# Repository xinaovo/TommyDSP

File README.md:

# TommyDSP

An audio DSP platform based on RP2350 microcontroller

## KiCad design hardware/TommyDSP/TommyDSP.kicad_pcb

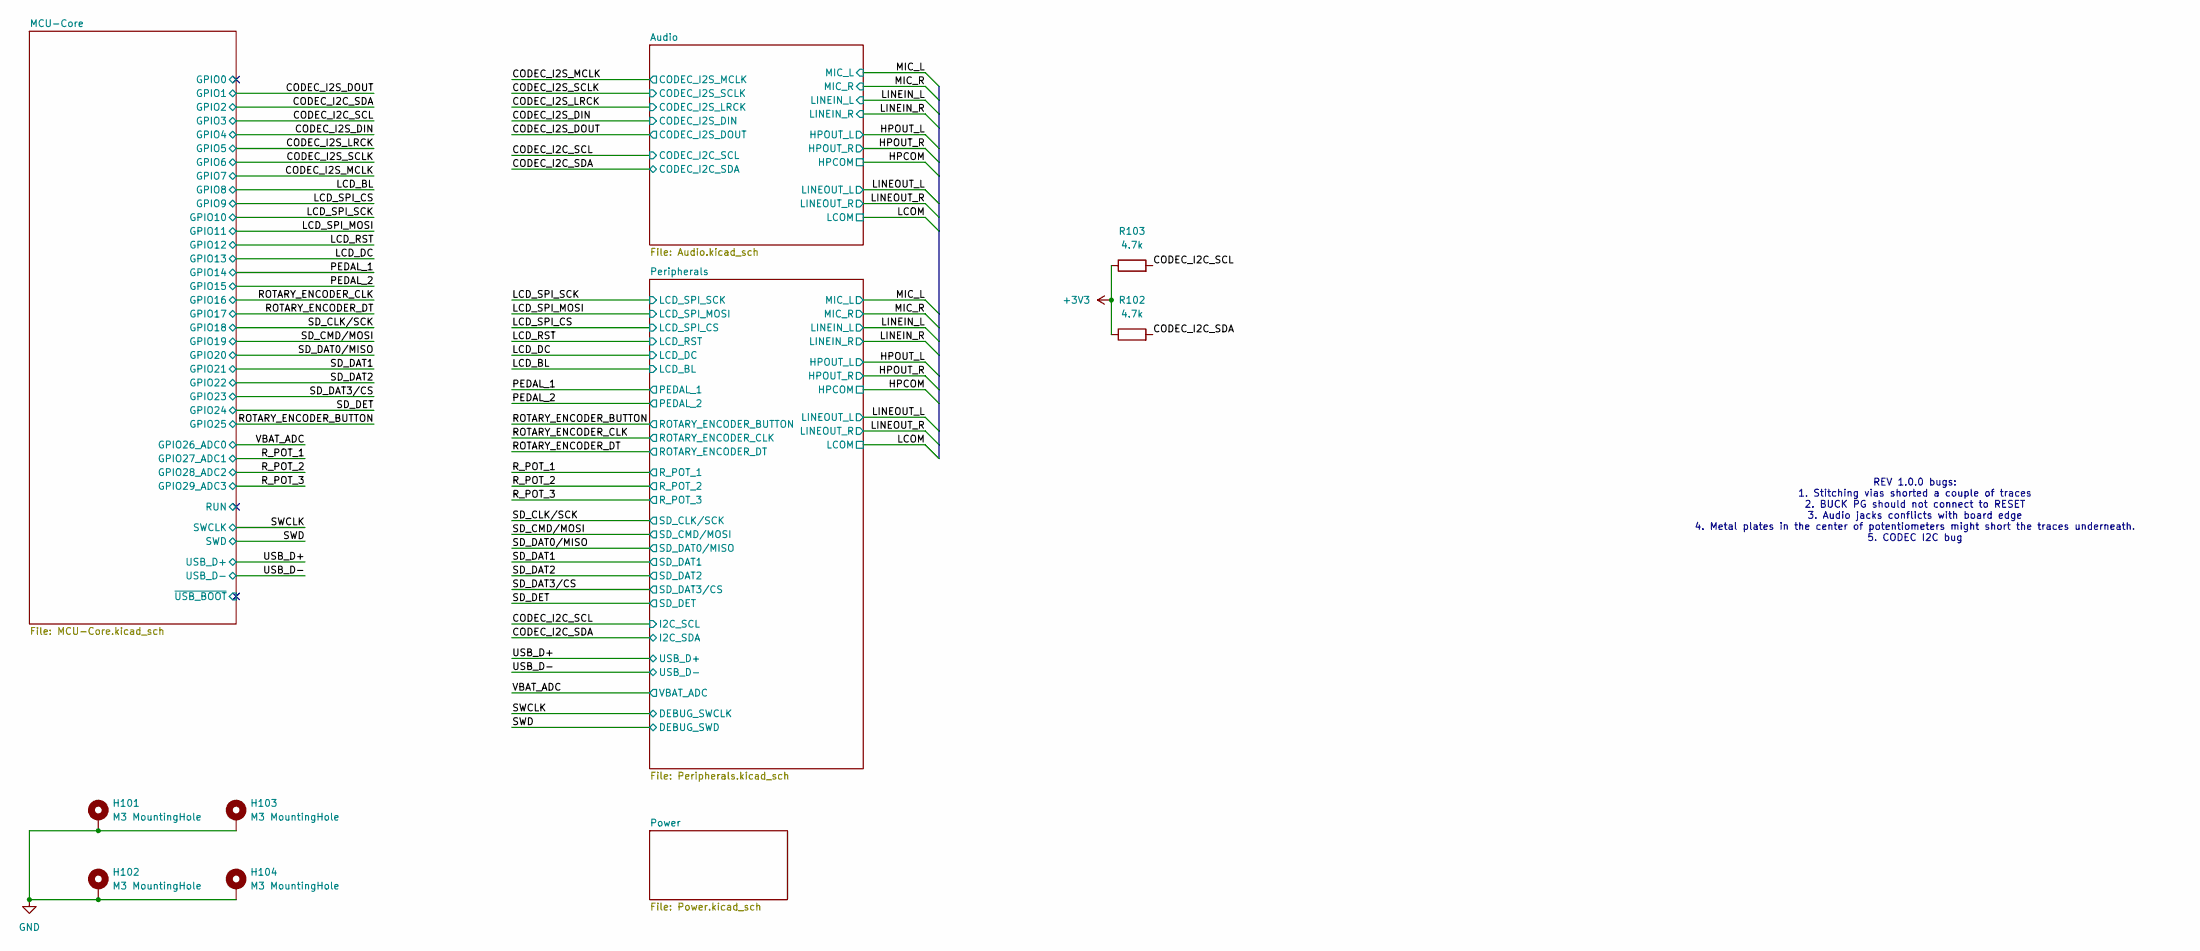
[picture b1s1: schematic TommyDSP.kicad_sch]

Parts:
H101, H102, H103, H104: M3 MountingHole; MountingHole_3.2mm_M3_DIN965_Pad_TopBottom
R102, R103: 4.7k; R_0603_1608Metric

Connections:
+3V3: R102.1, R103.1; also elsewhere on the board
/CODEC_I2C_SCL: R103.2; also elsewhere on the board
/CODEC_I2C_SDA: R102.2; also elsewhere on the board
GND: H101.1 (1_1), H102.1 (1_1), H103.1 (1_1), H104.1 (1_1); also elsewhere on the board

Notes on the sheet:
REV 1.0.0 bugs: 1. Stitching vias shorted a couple of traces 2. BUCK PG should not connect to RESET 3. Audio jacks conflicts with board edge 4. Metal plates in the center of potentiometers might short the traces underneath. 5. CODEC I2C bug

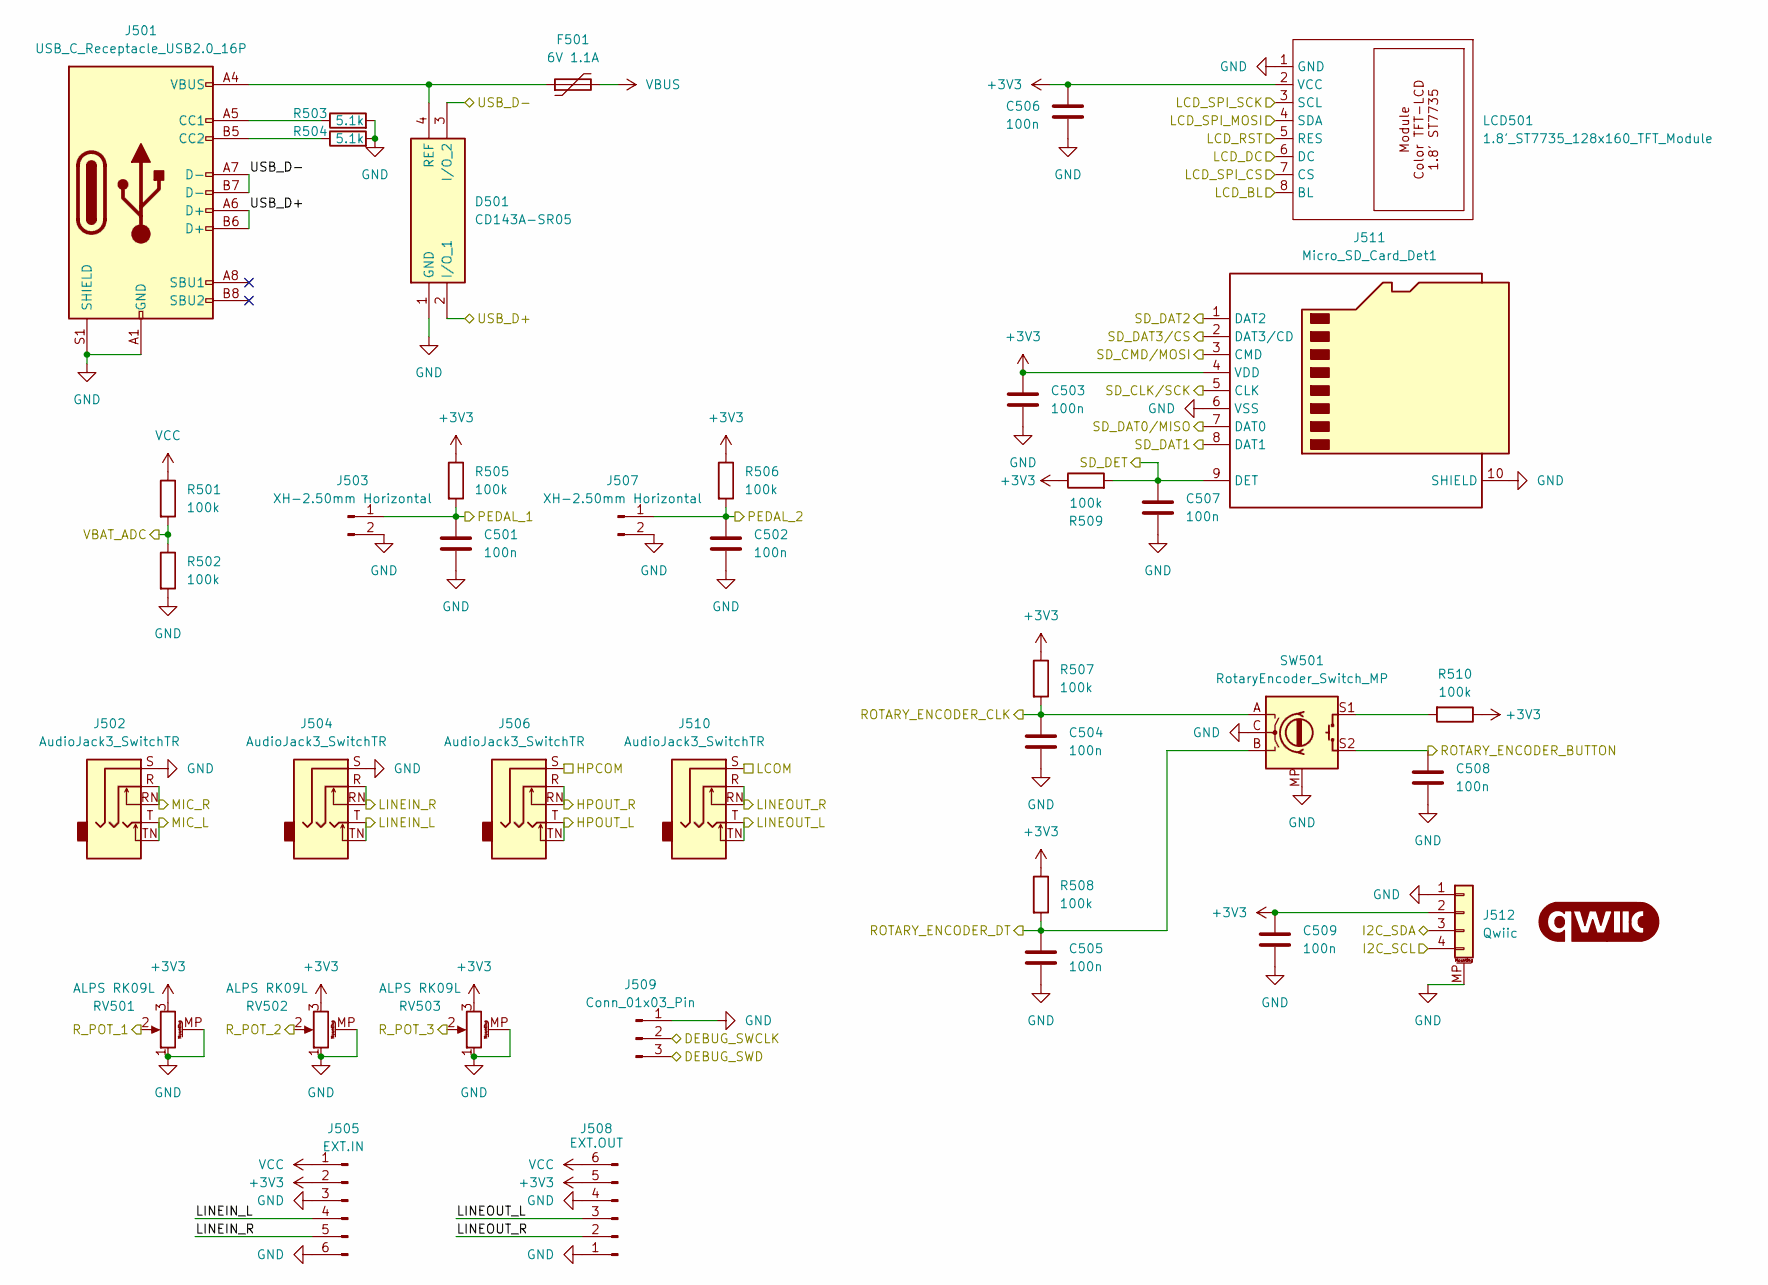
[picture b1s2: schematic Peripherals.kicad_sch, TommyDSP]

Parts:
C501, C502, C503, C504, C505, C506, C507, C508, C509: 100n; C_0603_1608Metric
D501: CD143A-SR05; CD143ASR05; Manufacturer_Part_Number CD143A-SR05; Mouser Part Number 652-CD143A-SR05
F501: 6V 1.1A; Fuse_1206_3216Metric
G501: qwiic_Logo; qwiic_5.5mm
J501: USB_C_Receptacle_USB2.0_16P; USB_C_Receptacle_G-Switch_GT-USB-7010ASV
J502, J504, J506, J510: AudioJack3_SwitchTR; Jack_3.5mm_CUI_SJ1-3525N_Horizontal
J503, J507: XH-2.50mm Horizontal; JST_EH_S2B-EH_1x02_P2.50mm_Horizontal
J505: EXT.IN; JST_XH_S6B-XH-A-1_1x06_P2.50mm_Horizontal
J508: EXT.OUT; JST_XH_S6B-XH-A-1_1x06_P2.50mm_Horizontal
J509: Conn_01x03_Pin; PinHeader_1x03_P2.54mm_Vertical
J511: Micro_SD_Card_Det1; TF01A
J512: Qwiic; JST_SH_SM04B-SRSS-TB_1x04-1MP_P1.00mm_Horizontal
LCD501: 1.8'_ST7735_128x160_TFT_Module
R501, R502, R505, R506, R507, R508, R509, R510: 100k; R_0603_1608Metric
R503, R504: 5.1k; R_0603_1608Metric
RV501, RV502, RV503: ALPS RK09L; Potentiometer_Alps_RK09K_Single_Vertical
SW501: RotaryEncoder_Switch_MP; RotaryEncoder_Alps_EC11E-Switch_Vertical_H20mm

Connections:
+3V3: C503.1, C506.1, C509.1, J505.2, J508.5, J511.4 (VDD), J512.2, LCD501.2 (VCC), R505.1, R506.1, R507.1, R508.1, R509.1, R510.1, RV501.3, RV502.3, RV503.3; also elsewhere on the board
/CODEC_I2C_SCL: J512.4; also elsewhere on the board
/CODEC_I2C_SDA: J512.3; also elsewhere on the board
/HPOUT_L: J506.T, J506.TN; also elsewhere on the board
/HPOUT_R: J506.R, J506.RN; also elsewhere on the board
/LCD_BL: LCD501.8 (BL); also elsewhere on the board
/LCD_DC: LCD501.6 (DC); also elsewhere on the board
/LCD_RST: LCD501.5 (RES); also elsewhere on the board
/LCD_SPI_CS: LCD501.7 (CS); also elsewhere on the board
/LCD_SPI_MOSI: LCD501.4 (SDA); also elsewhere on the board
/LCD_SPI_SCK: LCD501.3 (SCL); also elsewhere on the board
/LINEIN_L: J504.T, J504.TN, J505.4; also elsewhere on the board
/LINEIN_R: J504.R, J504.RN, J505.5; also elsewhere on the board
/LINEOUT_L: J508.3, J510.T, J510.TN; also elsewhere on the board
/LINEOUT_R: J508.2, J510.R, J510.RN; also elsewhere on the board
/MIC_L: J502.T, J502.TN; also elsewhere on the board
/MIC_R: J502.R, J502.RN; also elsewhere on the board
/PEDAL_1: C501.1, J503.1, R505.2; also elsewhere on the board
/PEDAL_2: C502.1, J507.1, R506.2; also elsewhere on the board
/ROTARY_ENCODER_BUTTON: C508.1, SW501.S2; also elsewhere on the board
/ROTARY_ENCODER_CLK: C504.1, R507.2, SW501.A; also elsewhere on the board
/ROTARY_ENCODER_DT: C505.1, R508.2, SW501.B; also elsewhere on the board
/R_POT_1: RV501.2; also elsewhere on the board
/R_POT_2: RV502.2; also elsewhere on the board
/R_POT_3: RV503.2; also elsewhere on the board
/SD_CLK/SCK: J511.5 (CLK); also elsewhere on the board
/SD_CMD/MOSI: J511.3 (CMD); also elsewhere on the board
/SD_DAT0/MISO: J511.7 (DAT0); also elsewhere on the board
/SD_DAT1: J511.8 (DAT1); also elsewhere on the board
/SD_DAT2: J511.1 (DAT2); also elsewhere on the board
/SD_DAT3/CS: J511.2 (DAT3/CD); also elsewhere on the board
/SD_DET: C507.1, J511.9 (DET), R509.2; also elsewhere on the board
/SWCLK: J509.2; also elsewhere on the board
/SWD: J509.3; also elsewhere on the board
/USB_D+: D501.2 (I/O_1), J501.A6 (D+_A6), J501.B6 (D+_B6); also elsewhere on the board
/USB_D-: D501.3 (I/O_2), J501.A7 (D-_A7), J501.B7 (D-_B7); also elsewhere on the board
/VBAT_ADC: R501.2, R502.1; also elsewhere on the board
GND: C501.2, C502.2, C503.2, C504.2, C505.2, C506.2, C507.2, C508.2, C509.2, D501.1 (GND), J501.A1 (GND_A1), J501.A12 (GND_A12), J501.B1 (GND_B1), J501.B12 (GND_B12), J501.S1 (SHIELD), J501.SH (SHIELD_S1), J502.S, J503.2, J504.S, J505.3, J505.6, J506.S, J507.2, J508.1, J508.4, J509.1, J510.S, J511.6 (VSS), J511.10 (SHIELD), J512.1, J512.MP (MountPin), LCD501.1 (GND), R502.2, R503.2, R504.2, RV501.1, RV501.MP (MountPin), RV502.1, RV502.MP (MountPin), RV503.1, RV503.MP (MountPin), SW501.C, SW501.MP; also elsewhere on the board
unnamed: D501.4 (REF), F501.1, J501.A4 (VBUS_A4), J501.A9 (VBUS_A9), J501.B4 (VBUS_B4), J501.B9 (VBUS_B9)
unnamed: J501.A5 (CC1_A5), R503.1
unnamed: J501.B5 (CC2_B5), R504.1
unnamed: R510.2, SW501.S1
VBUS: F501.2; also elsewhere on the board
VCC: J505.1, J508.6, R501.1; also elsewhere on the board

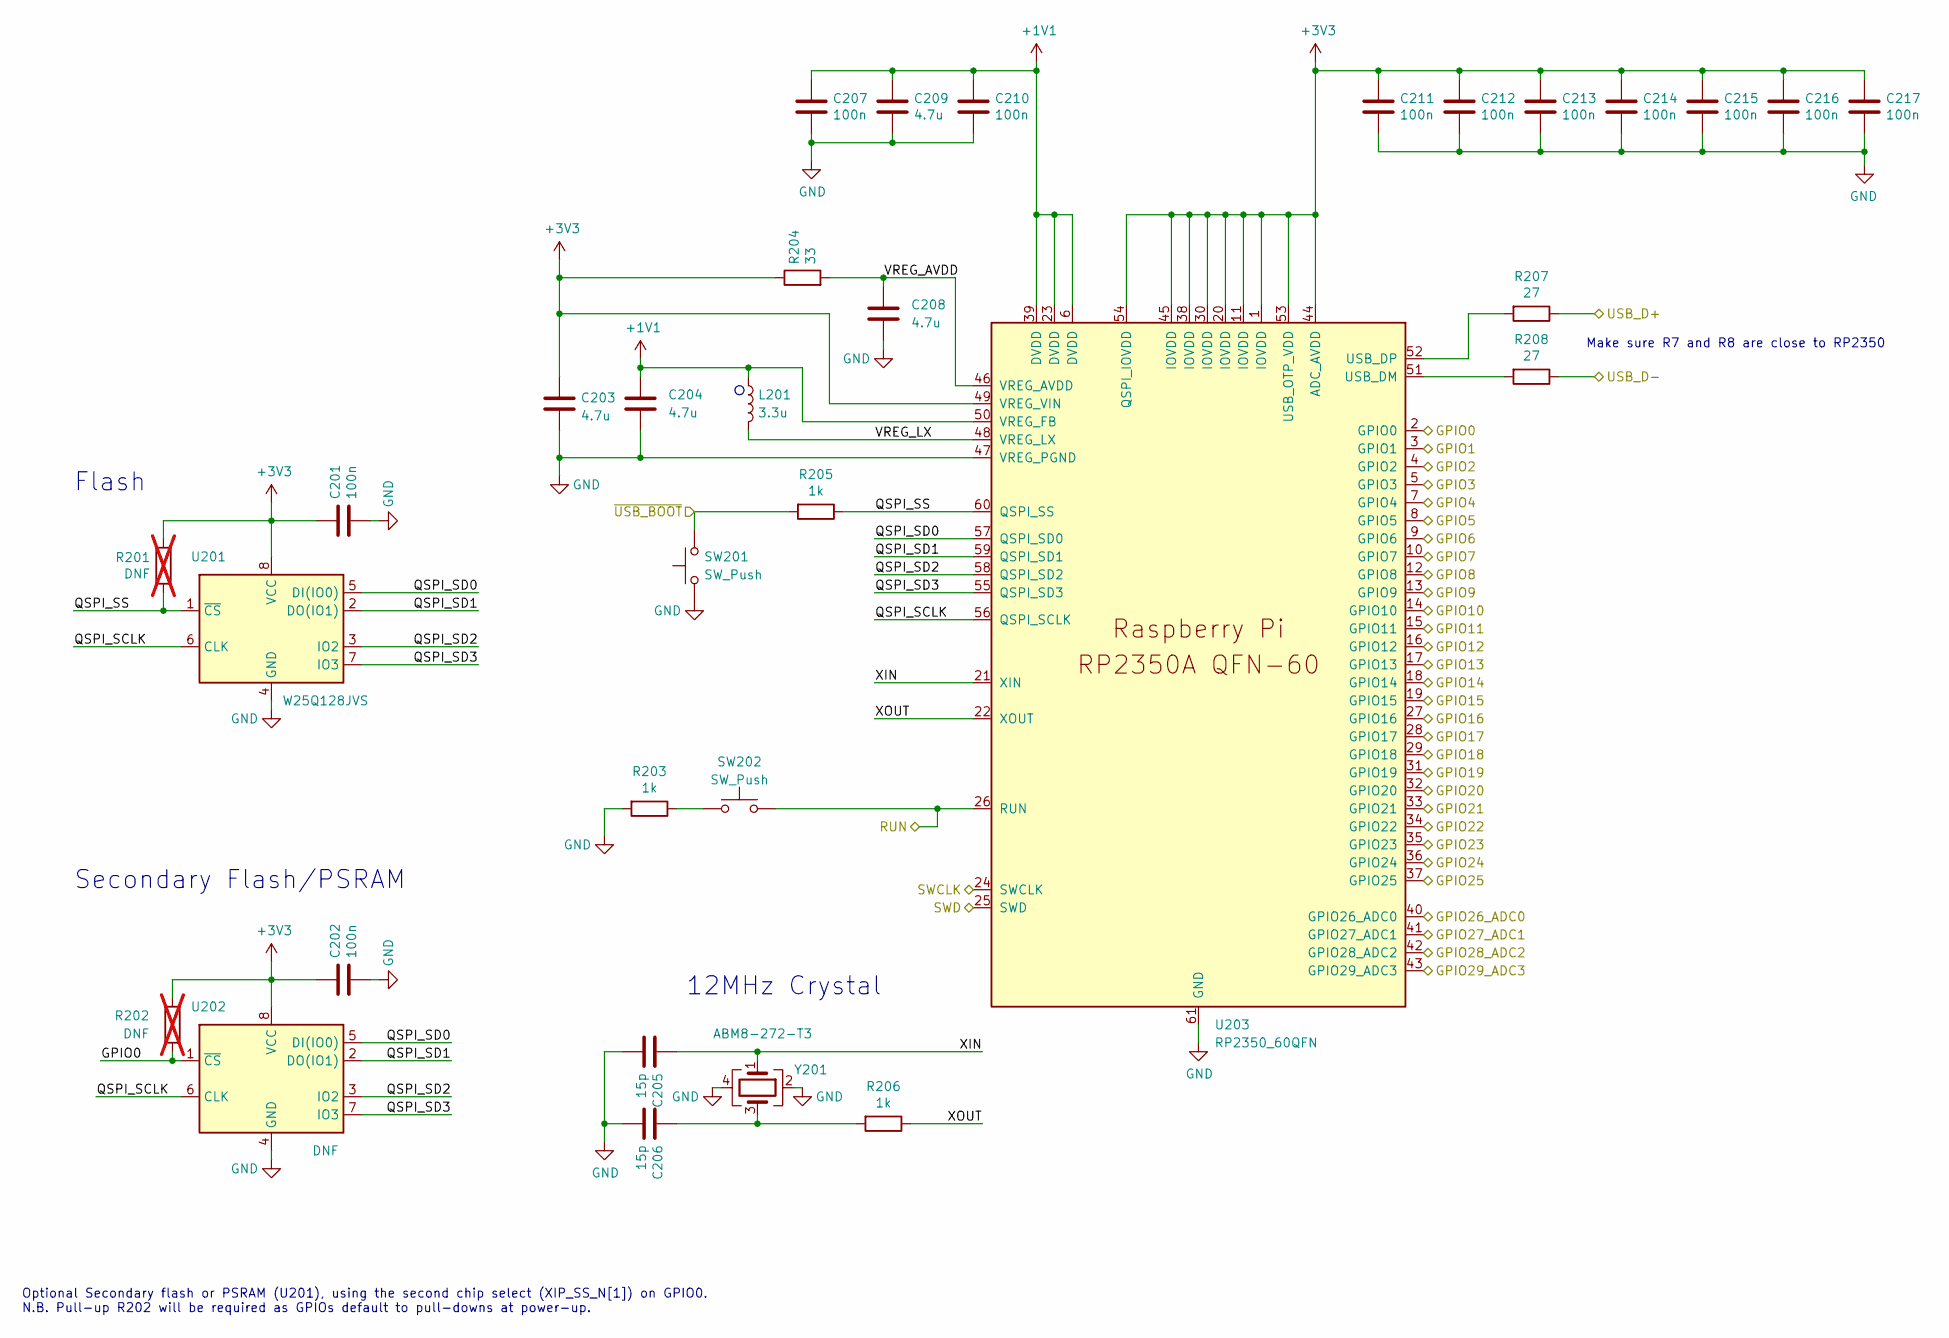
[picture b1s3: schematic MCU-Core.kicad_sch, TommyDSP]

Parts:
C201, C202: 100n; C_0603_1608Metric
C203, C204: 4.7u; C_0402_1005Metric_small_pads
C205, C206: 15p; C_0603_1608Metric
C207, C210, C211, C212, C213, C214, C215, C216, C217: 100n; C_0402_1005Metric
C208: 4.7u; C_0603_1608Metric
C209: 4.7u; C_0402_1005Metric
L201: 3.3u; L_pol_2016
R201, R202: DNF; R_0603_1608Metric; not fitted
R203, R205, R206: 1k; R_0603_1608Metric
R204: 33; R_0603_1608Metric
R207, R208: 27; R_0603_1608Metric
SW201, SW202: SW_Push; SW_SPST_CK_RS282G05A3
U201: W25Q128JVS; SOIC-8_5.3x5.3mm_P1.27mm
U202: DNF; SOIC-8_5.3x5.3mm_P1.27mm
U203: RP2350_60QFN; RP2350-QFN-60-1EP_7x7_P0.4mm_EP3.4x3.4mm_ThermalVias
Y201: ABM8-272-T3; Crystal_SMD_3225-4Pin_3.2x2.5mm

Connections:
+1V1: C204.1, C207.1, C209.1, C210.1, L201.1, U203.6 (DVDD), U203.23 (DVDD), U203.39 (DVDD), U203.50 (VREG_FB)
+3V3: C201.1, C202.1, C203.1, C211.1, C212.1, C213.1, C214.1, C215.1, C216.1, C217.1, R201.1, R202.1, R204.1, U201.8 (VCC), U202.8 (VCC), U203.1 (IOVDD), U203.11 (IOVDD), U203.20 (IOVDD), U203.30 (IOVDD), U203.38 (IOVDD), U203.44 (ADC_AVDD), U203.45 (IOVDD), U203.49 (VREG_VIN), U203.53 (USB_OTP_VDD), U203.54 (QSPI_IOVDD); also elsewhere on the board
/CODEC_I2C_SCL: U203.5 (GPIO3); also elsewhere on the board
/CODEC_I2C_SDA: U203.4 (GPIO2); also elsewhere on the board
/CODEC_I2S_DIN: U203.7 (GPIO4); also elsewhere on the board
/CODEC_I2S_DOUT: U203.3 (GPIO1); also elsewhere on the board
/CODEC_I2S_LRCK: U203.8 (GPIO5); also elsewhere on the board
/CODEC_I2S_MCLK: U203.10 (GPIO7); also elsewhere on the board
/CODEC_I2S_SCLK: U203.9 (GPIO6); also elsewhere on the board
/LCD_BL: U203.12 (GPIO8); also elsewhere on the board
/LCD_DC: U203.17 (GPIO13); also elsewhere on the board
/LCD_RST: U203.16 (GPIO12); also elsewhere on the board
/LCD_SPI_CS: U203.13 (GPIO9); also elsewhere on the board
/LCD_SPI_MOSI: U203.15 (GPIO11); also elsewhere on the board
/LCD_SPI_SCK: U203.14 (GPIO10); also elsewhere on the board
/MCU-Core/GPIO0: R202.2, U202.1 (~CS), U203.2 (GPIO0)
/MCU-Core/QSPI_SCLK: U201.6 (CLK), U202.6 (CLK), U203.56 (QSPI_SCLK)
/MCU-Core/QSPI_SD0: U201.5 (DI(IO0)), U202.5 (DI(IO0)), U203.57 (QSPI_SD0)
/MCU-Core/QSPI_SD1: U201.2 (DO(IO1)), U202.2 (DO(IO1)), U203.59 (QSPI_SD1)
/MCU-Core/QSPI_SD2: U201.3 (IO2), U202.3 (IO2), U203.58 (QSPI_SD2)
/MCU-Core/QSPI_SD3: U201.7 (IO3), U202.7 (IO3), U203.55 (QSPI_SD3)
/MCU-Core/QSPI_SS: R201.2, R205.1, U201.1 (~CS), U203.60 (QSPI_SS)
/MCU-Core/RUN: SW202.2, U203.26 (RUN)
/MCU-Core/VREG_AVDD: C208.1, R204.2, U203.46 (VREG_AVDD)
/MCU-Core/VREG_LX: L201.2, U203.48 (VREG_LX)
/MCU-Core/XIN: C205.1, U203.21 (XIN), Y201.1
/MCU-Core/XOUT: R206.1, U203.22 (XOUT)
/MCU-Core/~USB_BOOT: R205.2, SW201.2
/PEDAL_1: U203.18 (GPIO14); also elsewhere on the board
/PEDAL_2: U203.19 (GPIO15); also elsewhere on the board
/ROTARY_ENCODER_BUTTON: U203.37 (GPIO25); also elsewhere on the board
/ROTARY_ENCODER_CLK: U203.27 (GPIO16); also elsewhere on the board
/ROTARY_ENCODER_DT: U203.28 (GPIO17); also elsewhere on the board
/R_POT_1: U203.41 (GPIO27_ADC1); also elsewhere on the board
/R_POT_2: U203.42 (GPIO28_ADC2); also elsewhere on the board
/R_POT_3: U203.43 (GPIO29_ADC3); also elsewhere on the board
/SD_CLK/SCK: U203.29 (GPIO18); also elsewhere on the board
/SD_CMD/MOSI: U203.31 (GPIO19); also elsewhere on the board
/SD_DAT0/MISO: U203.32 (GPIO20); also elsewhere on the board
/SD_DAT1: U203.33 (GPIO21); also elsewhere on the board
/SD_DAT2: U203.34 (GPIO22); also elsewhere on the board
/SD_DAT3/CS: U203.35 (GPIO23); also elsewhere on the board
/SD_DET: U203.36 (GPIO24); also elsewhere on the board
/SWCLK: U203.24 (SWCLK); also elsewhere on the board
/SWD: U203.25 (SWD); also elsewhere on the board
/USB_D+: R207.1; also elsewhere on the board
/USB_D-: R208.1; also elsewhere on the board
/VBAT_ADC: U203.40 (GPIO26_ADC0); also elsewhere on the board
GND: C201.2, C202.2, C203.2, C204.2, C205.2, C206.2, C207.2, C208.2, C209.2, C210.2, C211.2, C212.2, C213.2, C214.2, C215.2, C216.2, C217.2, R203.2, SW201.1, U201.4 (GND), U202.4 (GND), U203.47 (VREG_PGND), U203.61 (GND), Y201.2, Y201.4; also elsewhere on the board
unnamed: C206.1, R206.2, Y201.3
unnamed: R203.1, SW202.1
unnamed: R208.2, U203.51 (USB_DM)
unnamed: R207.2, U203.52 (USB_DP)

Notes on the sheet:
Make sure R7 and R8 are close to RP2350
12MHz Crystal
Optional Secondary flash or PSRAM (U201), using the second chip select (XIP_SS_N[1]) on GPIO0. N.B. Pull-up R202 will be required as GPIOs default to pull-downs at power-up.
Flash
Secondary Flash/PSRAM

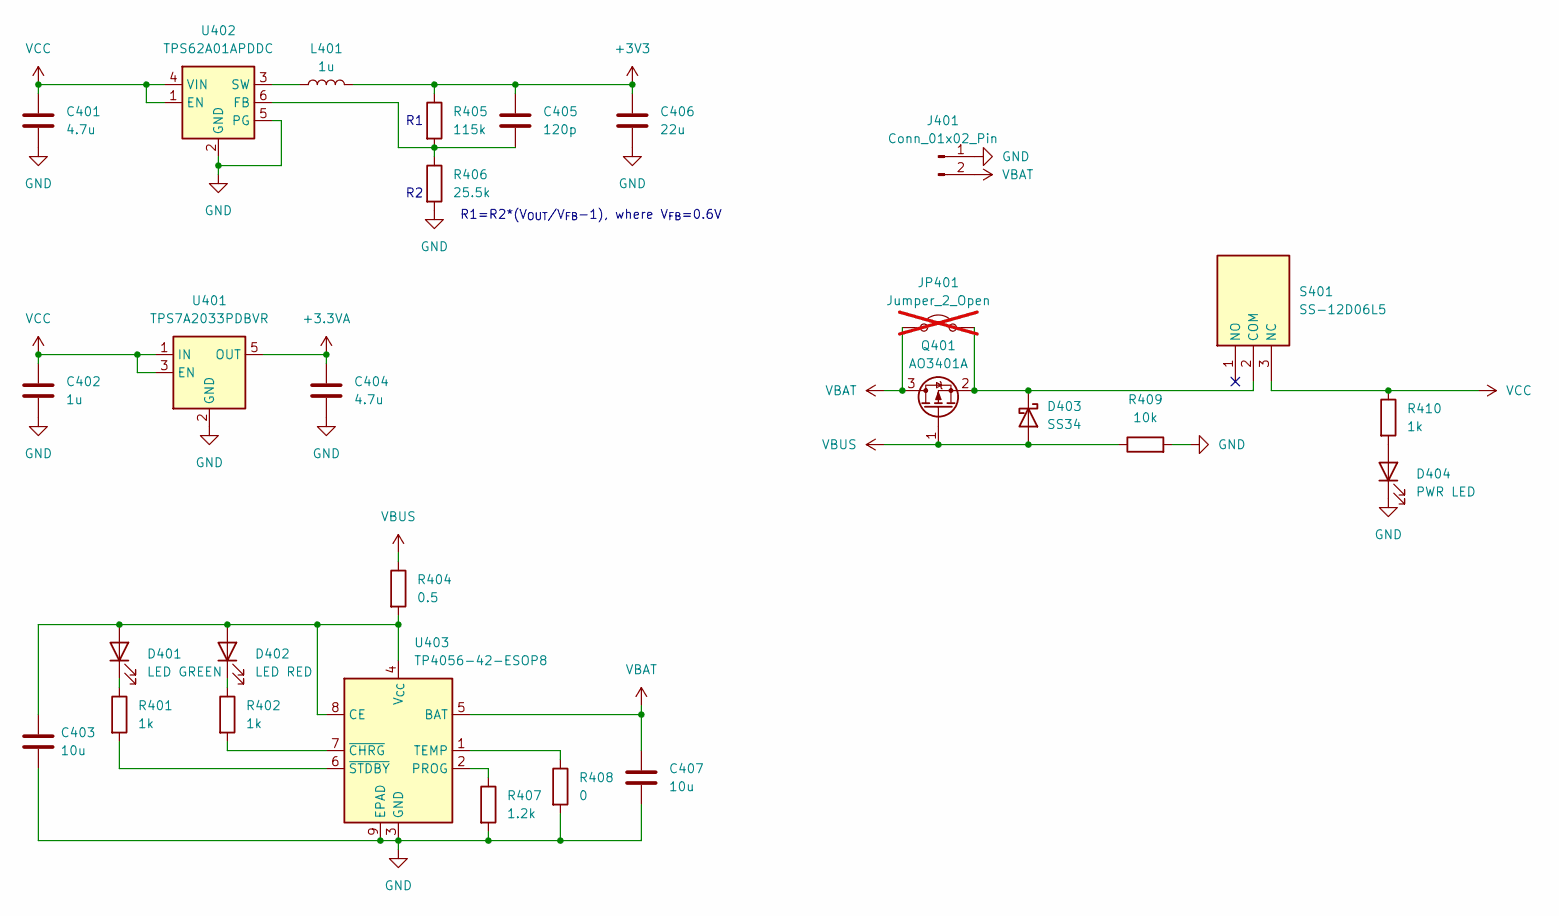
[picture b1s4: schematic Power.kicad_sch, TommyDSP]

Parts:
C401, C404: 4.7u; C_0603_1608Metric
C402: 1u; C_0603_1608Metric
C403, C407: 10u; C_0603_1608Metric
C405: 120p; C_0603_1608Metric
C406: 22u; C_0603_1608Metric
D401: LED GREEN; LED_0603_1608Metric
D402: LED RED; LED_0603_1608Metric
D403: SS34; D_SMA
D404: PWR LED; LED_D5.0mm
J401: Conn_01x02_Pin; JST_XH_B2B-XH-A_1x02_P2.50mm_Vertical
JP401: Jumper_2_Open; TestPoint_2Pads_Pitch2.54mm_Drill0.8mm; not fitted
L401: 1u; L_APV_ANR4020
Q401: AO3401A; SOT-23
R401, R402, R410: 1k; R_0603_1608Metric
R404: 0.5; R_1210_3225Metric
R405: 115k; R_0603_1608Metric
R406: 25.5k; R_0603_1608Metric
R407: 1.2k; R_0603_1608Metric
R408: 0; R_0603_1608Metric
R409: 10k; R_0603_1608Metric
S401: SS-12D06L5; SS12D06L5; Manufacturer_Part_Number SS-12D06L5
U401: TPS7A2033PDBVR; SOT-23-5
U402: TPS62A01APDDC; SOT-23-6
U403: TP4056-42-ESOP8; SOIC-8-1EP_3.9x4.9mm_P1.27mm_EP2.41x3.3mm_ThermalVias

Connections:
+3.3VA: C404.1, U401.5 (OUT); also elsewhere on the board
+3V3: C405.1, C406.1, L401.2, R405.1; also elsewhere on the board
GND: C401.2, C402.2, C403.2, C404.2, C406.2, C407.2, D404.1 (K), J401.1, R406.2, R407.2, R408.2, R409.2, U401.2 (GND), U402.2 (GND), U402.5 (PG), U403.3 (GND), U403.9 (EPAD); also elsewhere on the board
unnamed: C403.1, D401.2 (A), D402.2 (A), R404.2, U403.4 (V_{CC}), U403.8 (CE)
unnamed: D401.1 (K), R401.1
unnamed: D402.1 (K), R402.1
unnamed: D403.1 (K), JP401.2 (B), Q401.2 (S), S401.2 (COM)
unnamed: D404.2 (A), R410.2
unnamed: C405.2, R405.2, R406.1, U402.6 (FB)
unnamed: L401.1, U402.3 (SW)
unnamed: R407.1, U403.2 (PROG)
unnamed: R408.1, U403.1 (TEMP)
unnamed: R402.2, U403.7 (~CHRG)
unnamed: R401.2, U403.6 (~STDBY)
VBAT: C407.1, J401.2, JP401.1 (A), Q401.3 (D), U403.5 (BAT)
VBUS: D403.2 (A), Q401.1 (G), R404.1, R409.1; also elsewhere on the board
VCC: C401.1, C402.1, R410.1, S401.3 (NC), U401.1 (IN), U401.3 (EN), U402.1 (EN), U402.4 (VIN); also elsewhere on the board

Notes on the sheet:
R1=R2*(V_{OUT}/V_{FB}-1), where V_{FB}=0.6V
R1 R2

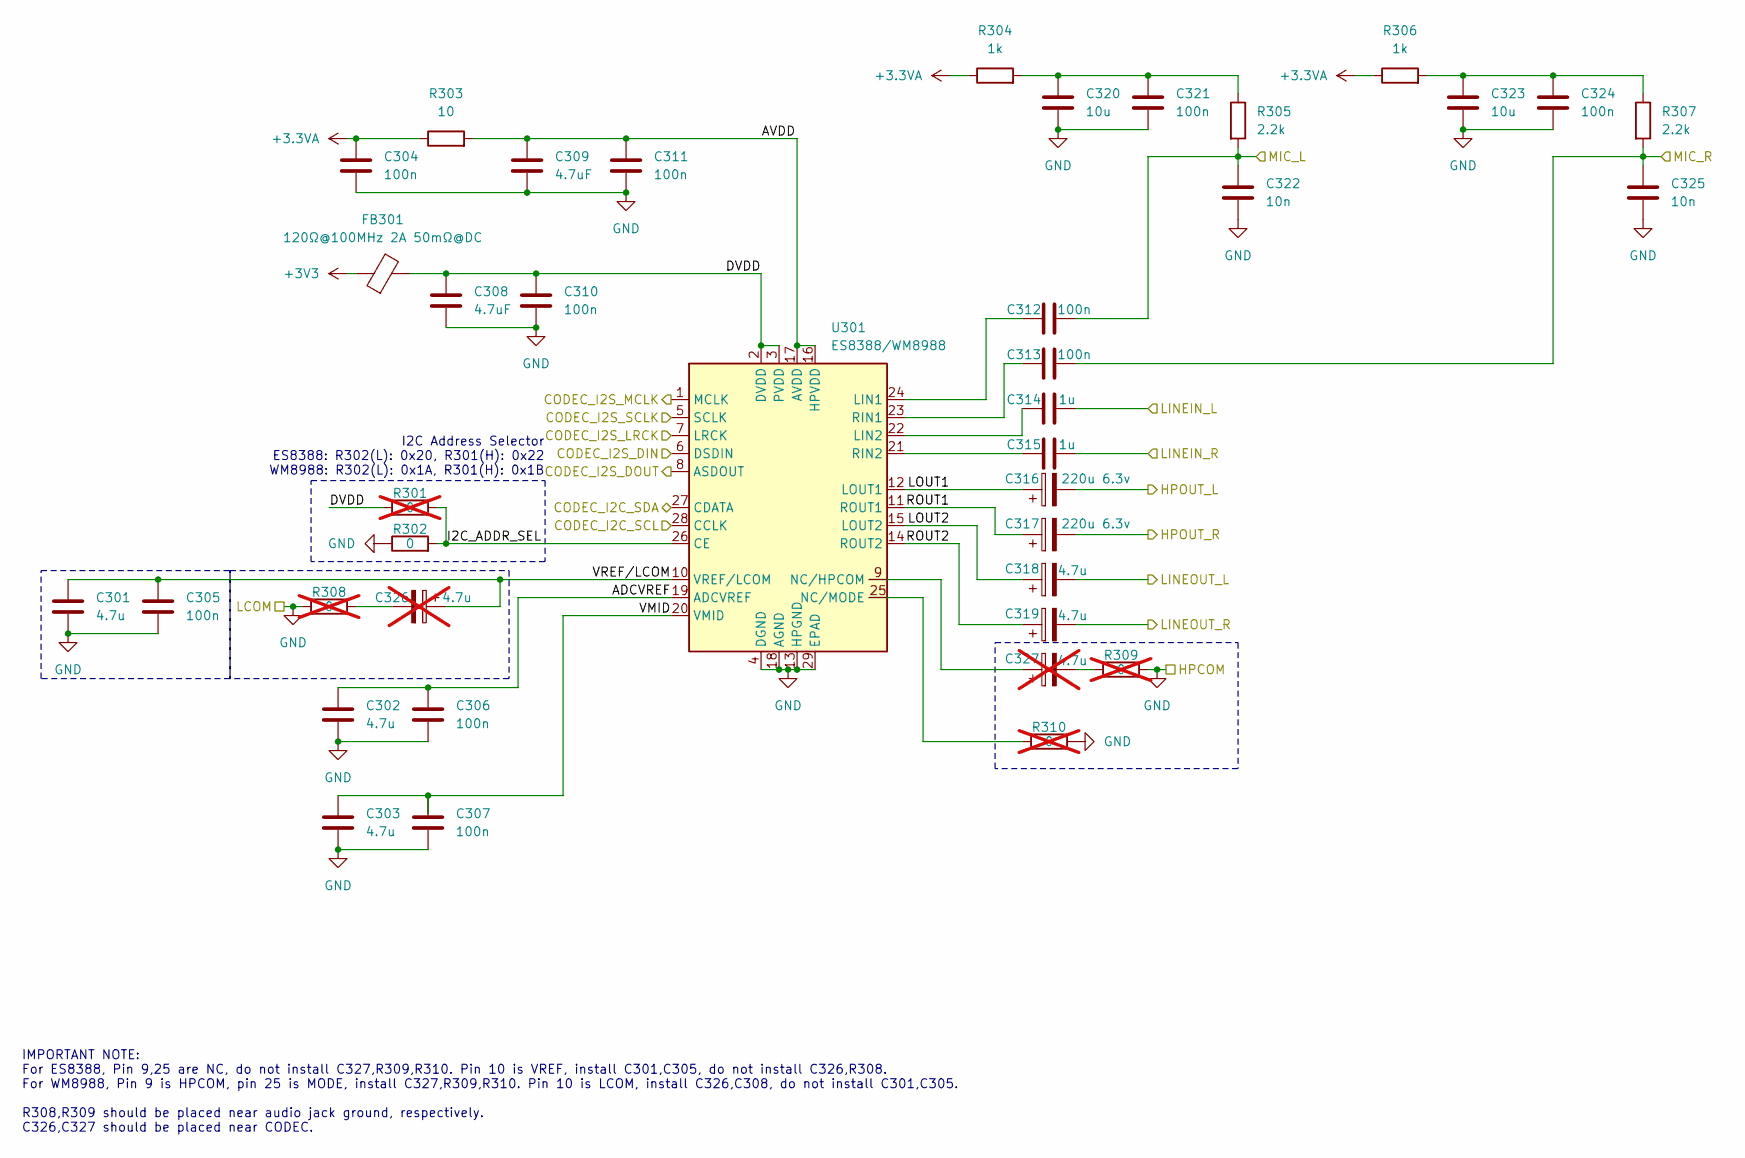
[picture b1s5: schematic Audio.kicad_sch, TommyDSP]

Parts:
C301, C302, C303: 4.7u; C_0603_1608Metric
C304, C305, C306, C307, C310, C311, C312, C313, C321, C324: 100n; C_0603_1608Metric
C308, C309: 4.7uF; C_0603_1608Metric
C314, C315: 1u; C_0603_1608Metric
C316, C317: 220u 6.3v; CP_Radial_D6.3mm_P2.50mm
C318, C319: 4.7u; CP_Radial_D5.0mm_P2.50mm
C320, C323: 10u; C_0603_1608Metric
C322, C325: 10n; C_0603_1608Metric
C326, C327: 4.7u; CP_Radial_D5.0mm_P2.50mm; not fitted
FB301: 120Ω@100MHz 2A 50mΩ@DC; L_0603_1608Metric
R301, R308, R309, R310: 0; R_0603_1608Metric; not fitted
R302: 0; R_0603_1608Metric
R303: 10; R_0603_1608Metric
R304, R306: 1k; R_0603_1608Metric
R305, R307: 2.2k; R_0603_1608Metric
U301: ES8388/WM8988; QFN-28-1EP_4x4mm_P0.45mm_EP2.6x2.6mm

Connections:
+3.3VA: C304.1, R303.1, R304.1, R306.1; also elsewhere on the board
+3V3: FB301.1; also elsewhere on the board
/Audio/ADCVREF: C302.1, C306.1, U301.19 (ADCVREF)
/Audio/AVDD: C309.1, C311.1, R303.2, U301.16 (HPVDD), U301.17 (AVDD)
/Audio/DVDD: C308.1, C310.1, FB301.2, R301.1, U301.2 (DVDD), U301.3 (PVDD)
/Audio/I2C_ADDR_SEL: R301.2, R302.2, U301.26 (CE)
/Audio/LOUT1: C316.1, U301.12 (LOUT1)
/Audio/LOUT2: C318.1, U301.15 (LOUT2)
/Audio/ROUT1: C317.1, U301.11 (ROUT1)
/Audio/ROUT2: C319.1, U301.14 (ROUT2)
/Audio/VMID: C303.1, C307.1, U301.20 (VMID)
/Audio/VREF/LCOM: C301.1, C305.1, C326.1, U301.10 (VREF/LCOM)
/CODEC_I2C_SCL: U301.28 (CCLK); also elsewhere on the board
/CODEC_I2C_SDA: U301.27 (CDATA); also elsewhere on the board
/CODEC_I2S_DIN: U301.6 (DSDIN); also elsewhere on the board
/CODEC_I2S_DOUT: U301.8 (ASDOUT); also elsewhere on the board
/CODEC_I2S_LRCK: U301.7 (LRCK); also elsewhere on the board
/CODEC_I2S_MCLK: U301.1 (MCLK); also elsewhere on the board
/CODEC_I2S_SCLK: U301.5 (SCLK); also elsewhere on the board
/HPOUT_L: C316.2; also elsewhere on the board
/HPOUT_R: C317.2; also elsewhere on the board
/LINEIN_L: C314.2; also elsewhere on the board
/LINEIN_R: C315.2; also elsewhere on the board
/LINEOUT_L: C318.2; also elsewhere on the board
/LINEOUT_R: C319.2; also elsewhere on the board
/MIC_L: C312.2, C322.1, R305.2; also elsewhere on the board
/MIC_R: C313.2, C325.1, R307.2; also elsewhere on the board
GND: C301.2, C302.2, C303.2, C304.2, C305.2, C306.2, C307.2, C308.2, C309.2, C310.2, C311.2, C320.2, C321.2, C322.2, C323.2, C324.2, C325.2, R302.1, R308.1, R309.2, R310.2, U301.4 (DGND), U301.13 (HPGND), U301.18 (AGND), U301.29 (EPAD); also elsewhere on the board
unnamed: C320.1, C321.1, R304.2, R305.1
unnamed: C323.1, C324.1, R306.2, R307.1
unnamed: C326.2, R308.2
unnamed: C327.2, R309.1
unnamed: C312.1, U301.24 (LIN1)
unnamed: C314.1, U301.22 (LIN2)
unnamed: C327.1, U301.9 (NC/HPCOM)
unnamed: R310.1, U301.25 (NC/MODE)
unnamed: C313.1, U301.23 (RIN1)
unnamed: C315.1, U301.21 (RIN2)

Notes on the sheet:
I2C Address Selector ES8388: R302(L): 0x20, R301(H): 0x22 WM8988: R302(L): 0x1A, R301(H): 0x1B
IMPORTANT NOTE: For ES8388, Pin 9,25 are NC, do not install C327,R309,R310. Pin 10 is VREF, install C301,C305, do not install C326,R308. For WM8988, Pin 9 is HPCOM, pin 25 is MODE, install C327,R309,R310. Pin 10 is LCOM, install C326,C308, do not install C301,C305. R308,R309 should be placed near a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

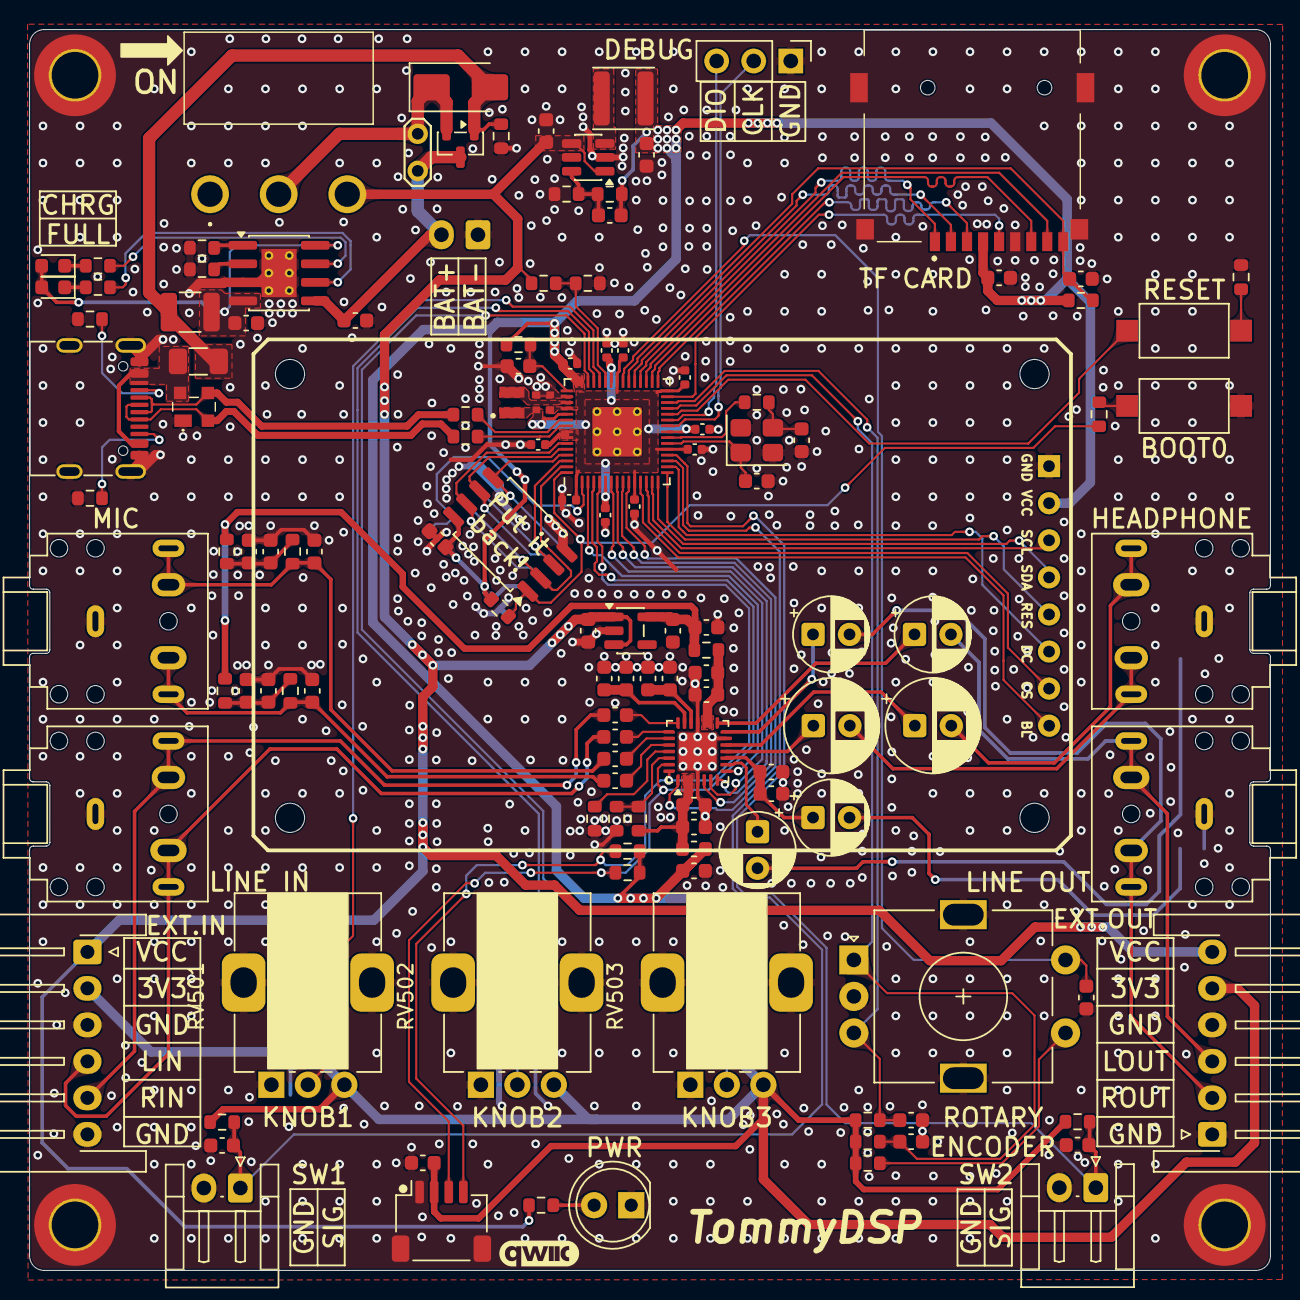
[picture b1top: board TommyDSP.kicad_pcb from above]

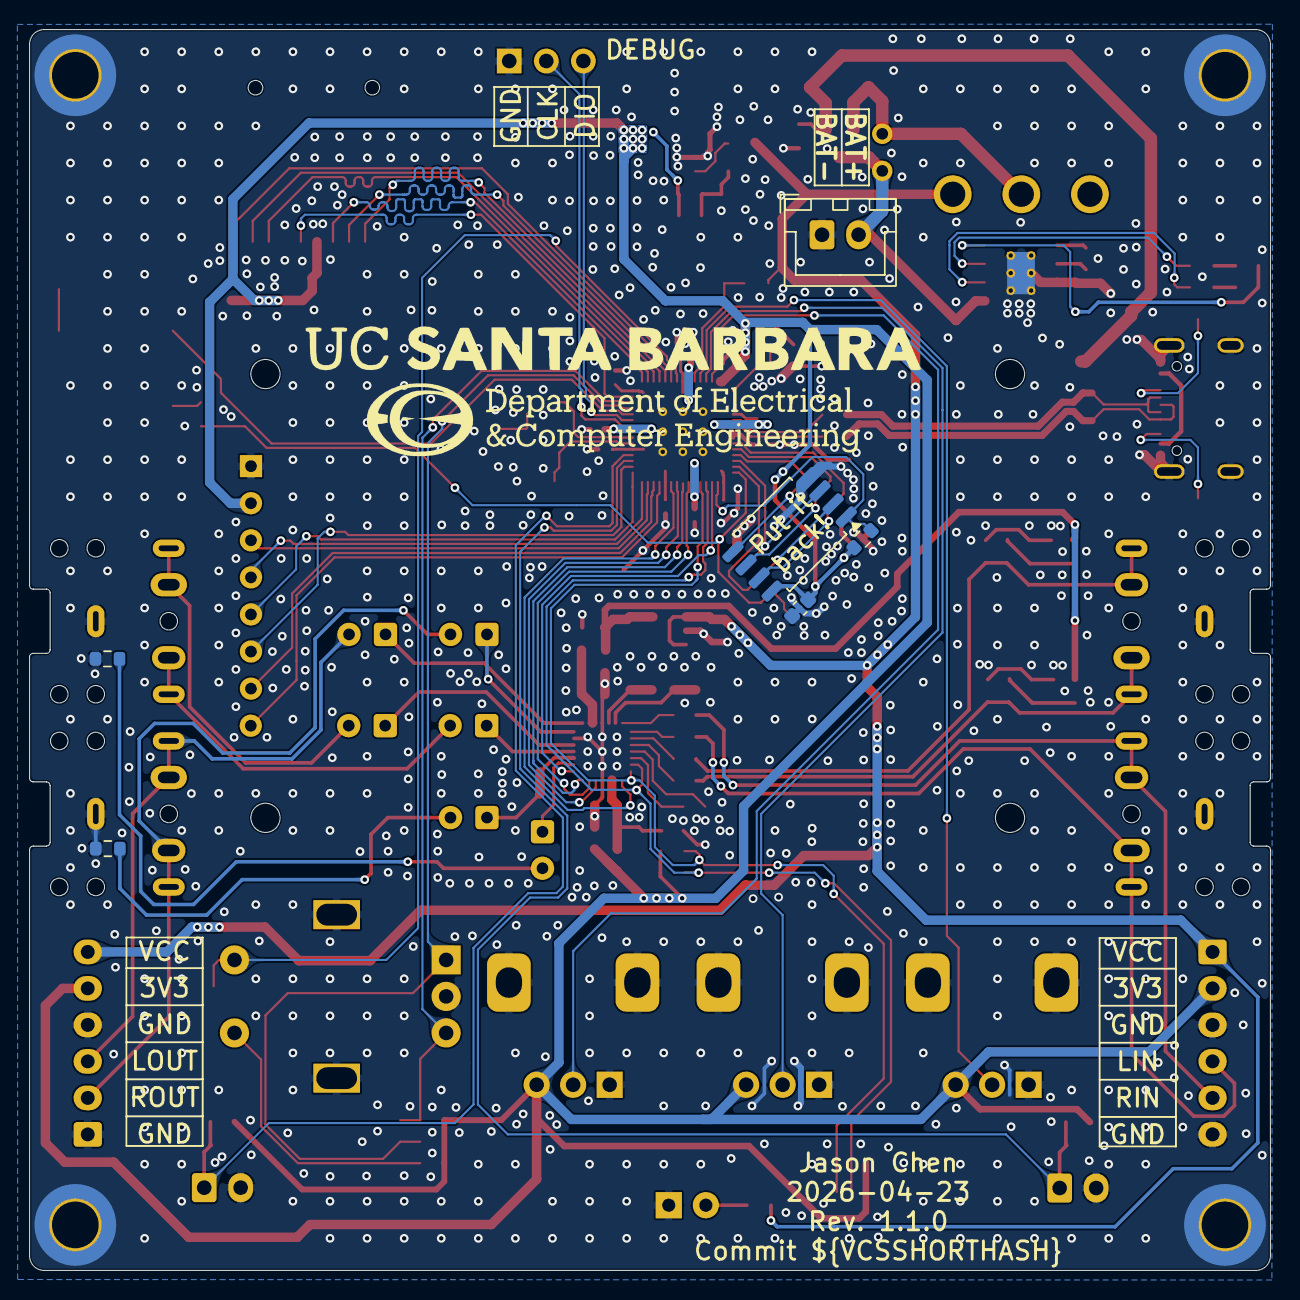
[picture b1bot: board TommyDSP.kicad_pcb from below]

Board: 2 copper layers, 85.0 x 85.0 mm, 144 parts (6 on the bottom side), 100 nets.
